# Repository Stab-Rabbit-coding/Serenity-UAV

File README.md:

<div align="center">

# Serenity UAV

### A flight-worthy, security-hardened EDF tilt-rotor replica of the Firefly-class ship *Serenity*

*"Can't stop the signal, and can't take the sky from me."*

*Isometric render of the Rev S assembly — port/bow/dorsal view. Predates the Rev S1g wing
spar and Rev S4c nacelle geometry; re-render pending (see `TODO.md` §0.10).*

</div>

## Overview

Serenity UAV is a fully functional electric ducted fan (EDF) tilt-rotor aircraft engineered as an
actual physical build of the Firefly-class transport *Serenity* (Joss Whedon, 2002) — every
component here is fabricated or procured, not conceptual. A two-part SLS-printed hull (one-piece forward head+cargo section and one-piece aft middle+rear section) carries two tilting EDF nacelles, a belly cargo bay with powered winch and clamshell doors,
and an 8-node cooperative avionics architecture with PACE (Primary/Alternate/Contingency/Emergency)
failover across every flight-critical function.

The design is held to the same rigor as a certifiable aircraft: real mass/CG/load budgets (no
"TBD" specs), FAA/FCC/NIST/IEC standards vetting on every design decision with any effect beyond
cosmetics, redundant power and control paths throughout, and a zero-trust security model — every
onboard message is signed, authenticated, and logged to hardware-enforced non-executable storage —
engineered to keep operating correctly inside a 500 W/m² RF field. Avionics, comms, and software
are built for reuse across other UAV/UGV/USV platforms, not just this airframe. See
[`AGENTS.md`](AGENTS.md) for the full authoritative project policy that governs every design
decision in this repository.

<table>
<tr>
<td width="50%" valign="top">

### Nominal Mission Profile

1. Take off VTOL.
2. Land vertically with cargo bay open and load and secure a 4″ × 3″ × 3″, 8 oz payload.
3. Take off VTOL with payload.
4. Fly into a 500 W/m² broadband RF environment.
5. Lower and release the payload from the cargo bay onto a platform.
6. Identify a 4″ × 3″ × 3″ payload on a moving platform.
7. Synchronize flight with the platform.
8. Attach the payload to the hoist and lift it from the platform.
9. Pull the payload into the cargo bay and close the clamshells.
10. Exit the hazardous environment and return to origin.

Throughout the mission, the aircraft shall also:

- Identify, categorize, log, and report rogue or unauthorized C2 commands or malicious logic from
  any transmitter, authorized or not.
- Identify unauthorized or unsafe behavior from any onboard compute node.
- Isolate the affected node(s), gracefully fail over its functions, and log/report to ground
  control — all while maintaining safety of flight.

</td>
<td width="50%" valign="top">

### Specifications

| Parameter | Value |
|-----------|-------|
| Length | 24.0 in (609 mm) |
| Wingspan | 19.1 in (486 mm) |
| Height | 7.93 in (201.5 mm) |
| AUW — two cells + 8 oz payload (Rev T-SB) | 13.93 lbm (6,318 g), provisional (`docs/flight_envelope.md`) |
| AUW — Phase 11 (full system) | not re-derived since the 64 mm / split-battery redesign |
| Payload capacity (minimum) | 8.0 oz (226 g) in a 4″ × 3″ × 3″ bay |
| Thrust — nacelles only | 20.90 lbf (9,480 g) = 4 × 83.60 ozf (2,370 gf), QF2822-2300KV at 24 V, 80 A ESCs |
| Thrust — Phase 11 rear EDF (cruise) | ~2.81 lbf (1,275 g) net after RCS bleed |
| T/W — nacelles only (hover) | ≈ 1.50 with payload (design floor 1.2; provisional pending mass truth) |
| T/W — Phase 11 (hover, nacelles only) | not re-derived |
| Compute | 8× PocketBeagle 2 Industrial (AM6254), PACE failover |
| Onboard buses | CAN FD, MIL-STD-1553C, RS-485, Ethernet RSTP ring |
| External comms | Five C2 links: Wi-Fi 5 GHz, Zigbee 2.4 GHz, mLRS, SiK/MAVLink 915 MHz, 49 MHz AX.25 |
| EMI design objective | 500 W/m² RF field, correct operation |

*Mass/thrust/T-W figures are the corrected 2026-08-22 baseline (the earlier 1.61 hover T/W used a
stale 2,768 g AUW) and remain provisional until the bottom-up AUW ledger recompute closes — see
`current-specification/README.md` and `docs/WBS.md` §0.10.1.*

</td>
</tr>
</table>

## Project Status (2026-11-03)

**Rev U, design and PCB layout. Nothing is fabricated or assembled; the physical build has not
started.** The path to first flight is in `docs/FIRST_FLIGHT_READINESS.md`; open work is in
[`TODO.md`](TODO.md), generated from the full record in [`WBS.md`](WBS.md).

| Area | State |
|------|-------|
| Airframe | SCAD shells at Rev S baseline, carried into Rev U; STL re-exports pending after the TACCO 60 × 35 mm change; cargo-shell mesh defect open |
| Nacelles | The 64 mm tandem-EDF nacelle (NAC-64-SERVO-01) with a servo-driven nozzle is the Rev U nacelle; the 50 mm nacelle is archived. Pivot (residual +9.6 mm), CFD, mass, and bench gates are open; the published pod STLs need a re-bake, and the 64 mm ESC bay covers are not yet generated (`tools/check_nacelle_deps.py`) |
| Avionics PCBs | Pilot and TACCO placed with ERC 0 / DRC 0 before routing, on corrected 4.80 mm PB2 rails; routing and Gerbers open. Flight Engineer, Observer, and Commo Rev T need further PCB work |
| Buses | Fleet MIL-STD-1553C via the Holt HI-6138 on every Pilot and TACCO (2026-09-28) |
| Comms | mLRS on a bare STM32WLE5JC; Wi-Fi USB module selection is a fab blocker; Commo becomes one standalone node (Rev T, 2026-09-29) |
| Firmware | `serenity-cn` Phase 6 done; `serenity-fc` Phase 6 stub; Phase 7 open |
| Ground station | Skipper in design; ground-side radio loadout decision open |
| BOM | `bom_revU` published 2026-11-03 (carry-forward of `bom_revT`, 2026-09-28); avionics rows lag the 2026-10 PCB changes |
| Build guide | Hand-drawn pre-Rev-T art; rebuild open (task 1.5.6) |

## Subsystems

<table>
<tr>
<td width="50%" valign="top">
<br><br>

**Airframe**

SLS-printed (DuraForm PA CF) hull with high-lift wings: in two sections (forward head+cargo and aft middle+rear), hollow-walled
and foam-filled to the canonical Firefly outer mold line. Rev S1g gave the wing a fixed,
bonded 20×16.3 mm carbon-fiber spar as its primary bending member, replacing the earlier
rotating-shaft design.

[Airframe README →](airframe/README.md)

</td>
<td width="50%" valign="top">
<br><br>

**Landing Gear**

Four corner legs pair a rigid CF-PETG post with spring and ductile wire braces, giving a
deliberately progressive, field-replaceable failure mode rated for a 6 ft full-AUW drop.

[Landing Gear Analysis →](docs/LANDING_GEAR_ANALYSIS.md)

</td>
</tr>
<tr>
<td width="50%" valign="top">
<br><br>

**Nacelles**

Two tilting pods each carry a tandem 64 mm EDF pair (QX-Motor QF2822-2300KV, 2,370 gf each), with a
variable-area nozzle scheduled on measured tilt (−5° to +135° pivot; 0° = horizontal) and driven by one KST X06
sub-micro servo per pod. The 64 mm pod is a uniform ×1.06 enlargement of the canonical shell with an integral
stage-1 motor plate and a removable stage-2 cartridge. The earlier 50 mm pods (Rev S4c) are archived.

[Nozzle-Drive Trade Study →](docs/NOZZLE_DRIVE_TRADE.md)

</td>
<td width="50%" valign="top">
<br><br>

**Powerplant**

Four nacelle EDFs give 9.84 lbf combined hover thrust at a T/W of ≈1.14, fed by a 6S LiPo through
the EMI-hardened Flight Engineer power distribution board.

[Power Distribution →](docs/POWER_DISTRIBUTION.md)

</td>
</tr>
<tr>
<td width="50%" valign="top">
<br><br>

**Avionics**

Eight PocketBeagle 2 Industrial nodes in four PACE-redundant stacks handle flight control, comms,
and payload functions, all with 5 kV galvanic isolation, TPM-backed signed logging, MIL-STD-1553C,
and a standalone **Commo** radio node (Rev T), plus the **Skipper** ground control station.

[Avionics README →](avionics/README.md)

</td>
<td width="50%" valign="top">
<br><br>

**Bow Sensor Suite**

The forward **Observer** node — camera, Time-of-Flight array, and an eye-safe laser indicator — in
the nose pod handles obstacle avoidance and rough size/orientation sizing of the mission payload.

[Observer Board →](avionics/kicad/Observer/Observer.md)

</td>
</tr>
<tr>
<td colspan="2" valign="top">
<br><br>

**Cargo Handling — Observer**

A belly clamshell cargo bay with a powered winch and hoist loads/releases an 8 oz payload in
flight, guided by the downward-facing **Observer** node for close-in 3D imaging of the payload.

[Cargo Winch Specification →](docs/CARGO_WINCH_SPECIFICATION.md)

</td>
</tr>
</table>

---

## Table of Contents

- [Project Status](#project-status-2026-10-07)
- [Authoritative Project Instructions](#authoritative-project-instructions)
- [References](#references)
- [License](#license)
- [Attribution](#attribution)
    - [Component License Map](#component-license-map)
    - [What This License Covers](#what-this-license-covers)
    - [Patent Notice](#patent-notice)
    - [Forensic Evidence Integrity Note](#forensic-evidence-integrity-note)

---

## Authoritative Project Instructions

The canonical workspace instructions and design policy are maintained in `AGENTS.md`. All
contributors and automated tools (including AI assistants) shall follow the requirements and
standards documented there (coding style, fabrication specs, licensing, and attribution).
`CLAUDE.md` is a one-line pointer to the same file, kept for tooling that looks for that name.

The [Nominal Mission Profile](#nominal-mission-profile) and [Specifications](#specifications)
above are the current design baseline. Full engineering detail for each subsystem lives in that
subsystem's own README/doc — see the link on each card in [Subsystems](#subsystems) above. The
narrative that used to live directly in this file (full Airframe/Powerplant/Avionics/Cargo
Handling write-ups) is preserved verbatim, for historical reference, in
[`archives/root-readme-deep-dive-2026-08-03.tar.gz`](archives/MANIFEST.md) (unpack per [`archives/README.md`](archives/README.md)).

---

## References

- Design conversation: [claude.ai/share/a1e3900e-d2bf-4690-ba63-25178e7de666](https://claude.ai/share/a1e3900e-d2bf-4690-ba63-25178e7de666)
- Latest design revision BOM: `current-specification/bom_revU.json` (Rev U, 2026-11-03)

---

## License

Licensed by Steve Griffing, PE(CSE), CISSP-ISSEP, CPP, according to what each file produces:

- **Hardware — and any code that defines, creates or renders hardware** (OpenSCAD,
  KiCad files and scripts, FreeCAD, Blender, G-code/slicer profiles, and tools that
  write or render meshes/CAD/PCB) — **CERN-OHL-W 2.0** (SPDX `CERN-OHL-W-2.0`).
  Full text: `LICENSE` (root) / `LICENSES/CERN-OHL-W 2.0`.
- **Code whose end result is software or firmware** (firmware, device trees, ground
  software, analysis/verification/CI tools) — **MIT** (SPDX `MIT`). Full text:
  `LICENSES/MIT`.
- **Documents** (Markdown, text, specifications, build guides, and all images — SVG,
  PNG, JPG, WebP, including renders produced by hardware tools) — **CC BY-SA 4.0**
  (SPDX `CC-BY-SA-4.0`). Full text: `LICENSES/CC-BY-SA 4.0`.

See `docs/attribution_and_licensing.md` for the full policy, the per-subsystem `LICENSE`
federation map, and the CERN-OHL-W "Available Component" treatment of upstream
canonical-reference geometry. Revision U, November 2026.

## Attribution

> "Serenity Tiltrotor Drone Project — hardware CERN-OHL-W 2.0, software MIT, docs CC BY-SA 4.0, based on:
> · Serenity Firefly-class hull by misubisu (thingiverse.com/thing:7330462, CC BY-SA 4.0)
> · Variable-area EDF nozzle by BamJr (thingiverse.com/thing:2991269, CC BY 4.0)
> Include a link to the applicable license and indicate if changes were made."

### Component License Map

| Component | Original Author | Source | License | Derivative Notes |
|-----------|----------------|--------|---------|-----------------|
| Hull | misubisu | [thingiverse.com/thing:7330462](https://www.thingiverse.com/thing:7330462) | CC BY-SA 4.0 (Available Component under CERN-OHL-W 2.0) | Scaled to 24 in, hollowed to 0.079 in (2.0 mm) CF-PETG shell, foam-filled |
| Nozzle mechanism concept | BamJr | [thingiverse.com/thing:2991269](https://www.thingiverse.com/thing:2991269) | CC BY 4.0 | Iris petal concept reference; all Rev O/P/Q nozzle geometry original |
| Design (hardware/CAD/PCB) | This project | — | CERN-OHL-W 2.0 | All original work: PCBs, mechanical/CAD, wiring |
| Design (docs/code/scripts) | This project | — | CC BY-SA 4.0 | Firmware spec, tooling, build guides, this document |

### What This License Covers

Covered under **CERN-OHL-W 2.0** (hardware):

- 3D-printable hull, nacelle, and nozzle design files (STL/SCAD/FCStd)
- PCB schematics and Gerber files for Pilot, TACCO, Flight Engineer, Commo, and Observer
- Circuit diagrams, pinout tables, and wiring specifications
- Mechanical drawings and assembly specifications
- Any derived hardware shall carry CERN-OHL-W 2.0 (or a compatible license) and attribute
  all upstream authors

Covered under **CC BY-SA 4.0** (documentation, code, scripts, non-hardware drawings):

- Firmware architecture specifications and algorithm descriptions
- This design document in all its revisions (A–R and beyond)
- Build automation/tooling scripts and non-hardware SVG diagrams
- Any derived works shall carry CC BY-SA 4.0 and attribute all upstream authors

Not covered / separate terms:

- Third-party commercial components (EDFs, ESCs, PocketBeagle 2, etc.) — their own terms
- SiK radio firmware — GPL-3.0
- ArduPilot / QGroundControl — GPL-3.0
- tpm2-tools / tpm2-tss — BSD-2
- CPLD Verilog write-blocker firmware — separately MIT licensed
- Proprietary flight controller firmware (your compiled code) — your terms
- FAA/ICAO regulatory compliance is YOUR responsibility as operator

### Patent Notice

This license does NOT grant rights to any patents held by component manufacturers or the
design authors. The design uses standard open hardware interfaces (CAN FD, Ethernet, SDIO,
SPI, I²C, MAVLink). If you commercialise products based on this design, conduct your own
freedom-to-operate analysis. The write-blocker CPLD design implements append-only log
enforcement consistent with log data protection principles in NIST SP 800-92 §4.4.2
[REF-NIST-004]; no patent claims are made on the implementation.

### Forensic Evidence Integrity Note

The write-blocker and NX enforcement hardware described in this design are intended to
support operational log integrity, not forensic evidence collection.  They implement
log data protection principles consistent with NIST SP 800-92 §4.4.2 [REF-NIST-004].
They are NOT certified forensic tools under NIST CFTT (Computer Forensics Tool Testing)
Program specifications or SWGDE (Scientific Working Group on Digital Evidence) standards.
Do not use this design as the sole mechanism for evidence preservation in legal proceedings
without independent verification of the implementation against your jurisdiction's
evidence handling requirements.

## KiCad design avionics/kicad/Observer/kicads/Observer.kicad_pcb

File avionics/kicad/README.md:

# Serenity Avionics — KiCad Board Index and Status

**Last updated:** 2026-10-07
**License:** CC BY-SA 4.0 — creativecommons.org/licenses/by-sa/4.0 (SPDX-License-Identifier: CC-BY-SA-4.0)

This directory holds the KiCad projects, generator scripts, and status files for every Serenity
avionics board. **Each board's own `.md` file is the authoritative as-built status**
(`avionics/AGENTS.md`, "Cape Naming and Revision History"); the table below is a dated
snapshot, so confirm against the board file before relying on it for fabrication or integration.
KiCad files keep KiCad board coordinates (a documented exception to the hull-frame standard,
see root `AGENTS.md`).

## Boards

| Folder | Board | Role | Status file |
| --- | --- | --- | --- |
| `Pilot/` | **Pilot** | PB2-I cape: flight control and sensors | `Pilot/Pilot.md` |
| `TACCO/` | **TACCO** | PB2-I cape: comms, logging, payload | `TACCO/TACCO.md` |
| `FlightEngineer/` | **Flight Engineer** | Power Distribution Board (PDB) | `FlightEngineer/FlightEngineer.md` |
| `Commo/` | **Commo** | 49 MHz + SiK transceiver; Rev S was a PB2-I cape, Rev T is a standalone bus node | `Commo/Commo.md` |
| `Observer/` | **Observer** | Standalone nose/cargo-bay vision, ToF, and laser board | `Observer/Observer.md` |
| `Bus-Gateway/` | **CAN-PERIPH-GW-1** | Secure CAN-FD / RS-485 edge node | `Bus-Gateway/CAN-PERIPH-GW-1.md` |
| `Encoder/` | **ENC-NACELLE-1** | Nacelle tilt-angle encoder (AK7455) | `Encoder/ENC-NACELLE-1.md` |

The legacy working name "XO" for TACCO survives only in some script and file names.

## Status snapshot (2026-10-07)

| Board | ERC | DRC | Placement | Routing | Gerbers |
| --- | --- | --- | --- | --- | --- |
| Pilot | 0 errors | 0 errors, parity 0 | 120 of 120 placed | Not started (0% routed) | Open |
| TACCO | 0 errors | 0 errors, parity 0 (before routing) | 163 parts placed on a 60 × 35 mm outline | Not started (0 segments) | Open; the checked-in set predates the rebuild |
| Flight Engineer | 0 errors | 29–31 hard violations | 151 of 151 placed | Not started | Open |
| Commo | Rev S: 0 errors | Rev S closed, not worked further | Rev T in design | Rev T outline and placement open | Rev S Gerbers will not be built |
| Observer | 0 errors | 124 hard violations | Initial shelf-pack; PCB predates the schematic | Not started; PCB resync not started | Open |
| Bus-Gateway | 0 errors | 1 hard violation | Placed (`N_STACKS=4`) | About 84% routed | Generated at that state |
| Encoder | 0 errors | 0 hard violations | Complete | Complete | Open item: firmware and bench calibration |

Pilot and TACCO both use Samtec TSM-118-04-L-DV-LC male SMT rails at 4.80 mm from each long
board edge (PB2 System Reference Manual Fig. 3.45, REF-SENSOR-041). A fab blocker is open on
TACCO: the owner has yet to select the USB Wi-Fi module (`avionics/WBS.md` §1.2a). The open-item
list for every board is in `avionics/TODO.md`; the full record is `avionics/WBS.md`.

## Supporting files

| Path | Purpose |
| --- | --- |
| `PB2_HEADER_PINMAP.md` | Verified PocketBeagle 2 P1/P2 ball-by-ball map and the TACCO allocation |
| `HI6138_FOOTPRINT_VERIFICATION.md` | Holt HI-6138 (MIL-STD-1553C) pin table and area budget |
| `Serenity-Custom.pretty/`, `symbols/` | Project footprint and symbol libraries |
| `tools/swap_1553_hi6138.py` | The fleet 1553C swap script (this folder's `tools/`) |
| `gerbers/` | Legacy Rev S1 Gerber sets; per-board sets are under each board folder (check its status file for currency) |
| `TODO-1.2b-*.md` | Archived (moved to `archives/rev-T-and-earlier/avionics/kicad/`): superseded 2026-07-18 task snapshots; the live record is `avionics/WBS.md` §1.2a |

## Design method

Pilot, TACCO, Flight Engineer, and the Bus-Gateway use a **schematic-first generator** workflow:
a Python generator under `<board>/scripts/` writes both the schematic and the PCB, so the two
stay in parity. Edit the generator, not the generated files, except where a board file says the
owner has taken manual control of placement. Final component placement is the owner's
(root `AGENTS.md` §5); refer any DRC violation that needs a footprint moved to the owner.
Every schematic or PCB edit needs a KiCad ERC and DRC pass (root `AGENTS.md` §7).

## Toolchain findings (headless KiCad 9 and freerouting)

Recorded so the next contributor does not re-derive them:

- **`pcbnew.ExportSpecctraDSN()` does not work in standalone Python** under KiCad 9.0.2: it
  returns `False` because there is no GUI context. The project uses a custom headless Specctra
  DSN exporter and SES importer (repo-root `tools/export-specctra-dsn.py`, `tools/import-specctra-ses.py`)
  that round-trip correctly.
- **freerouting 2.2.4** exits by itself after its passes and gave the Bus-Gateway its ~84%
  route. Run it without a display, with `-mt 1`. It writes the `.ses` only at the end of a run,
  and its passes take minutes each, so budget the full run. The earlier 2.1.0 build never
  self-exited and captured only a handful of nets; do not use it.
- **Pilot's two runs were rejected** (see "Routing status" in `Pilot/Pilot.md`): automated
  results that introduced shorts are reported, not accepted.
- Route the impedance-controlled Ethernet pairs interactively, length-matched, regardless of
  autorouter results.
- The tamper-mesh rework (per-domain meshes, tamper signals for TPM-less boards) is open
  work in `avionics/WBS.md` §1.2a.1.

---

*Author: Steve Griffing, PE(CSE), CISSP-ISSEP, CPP · License: CC BY-SA 4.0*

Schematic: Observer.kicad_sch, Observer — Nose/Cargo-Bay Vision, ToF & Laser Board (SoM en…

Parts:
CMC5: SRF2012-100Y (CAN); L_CommonModeChoke_Coilcraft_0805USB
C_2V5I, C_2V5O: 1uF; C_0402_1005Metric
C_ADM1, C_ADM2: 100nF; C_0402_1005Metric
C_ISO: 100nF/500V; C_0402_1005Metric
C_VCORE: 1uF; C_0402_1005Metric
C_VISO: 1uF; C_0402_1005Metric
D5: PRTR5V0U2X; SOT-143
J_CAM1: CSI CLK/D0; JST_GH_BM04B-GHS-TBT_1x04-1MP_P1.25mm_Vertical
J_CAM2: CAM SDA/SCL/RST/3V3; JST_GH_BM04B-GHS-TBT_1x04-1MP_P1.25mm_Vertical
J_CAM_DS: Direct-solder camera land (nose; DNP if J_CAM* us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; DS_Camera_9P
J_CANFD: 5V/CANH/CANL/GND; JST_GH_BM04B-GHS-TBT_1x04-1MP_P1.25mm_Vertical
J_CHASSIS_R: 0R; R_0402_1005Metric
J_ETH_IN: JST-GH 5P shielded Eth ring; JST_GH_SM05B-GHS-TB_1x05-1MP_P1.25mm_Horizontal
J_ETH_OUT: JST-GH 5P shielded Eth ring; JST_GH_SM05B-GHS-TB_1x05-1MP_P1.25mm_Horizontal
J_LASER: laser +5V/cathode; JST_SH_BM02B-SRSS-TB_1x02-1MP_P1.00mm_Vertical
J_LASER_DS: Direct-solder laser land (nose; DNP if J_LASER us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; DS_Laser_2P
J_PWR: JST-GH 2P +5V/GND; JST_GH_BM02B-GHS-TBT_1x02-1MP_P1.25mm_Vertical
J_RS485_IN: RS-485 trunk IN (A/B/GND)
J_RS485_OUT: RS-485 trunk OUT (A/B/GND)
J_SWD: SWD: DIO/CLK/NRST/GND; JST_GH_BM04B-GHS-TBT_1x04-1MP_P1.25mm_Vertical
J_TOF: TFmini-S 5V/GND/TX/RX; JST_GH_BM04B-GHS-TBT_1x04-1MP_P1.25mm_Vertical
J_TOF_DS: Direct-solder ToF land (nose; DNP if J_TOF used); DS_ToF_4P
Q1: AO3400 logic-level N-MOSFET; SOT-23
R1: 100R gate; R_0402_1005Metric
R2: 10k pulldown; R_0402_1005Metric
R_485TERM: 120R; R_0402_1005Metric
R_FB1B, R_FB1T, R_FB3B: 100k 1%; R_0402_1005Metric
R_FB3T: 453k 1%; R_0402_1005Metric
R_ISET: 6.04k; R_0402_1005Metric
R_NRST: 10k; R_0402_1005Metric
R_PG1, R_PG3: 100k; R_0402_1005Metric
R_PORZ: 10k; R_0402_1005Metric
R_REXT: 191R; R_0402_1005Metric
R_SHIELD: 0R; R_0402_1005Metric
SJ_485: open by default; SolderJumper-2_P1.3mm_Open_Pad1.0x1.5mm
T1, T2: Wurth 749010012A; Wurth_749010012A_10-100BASE-TX
T1_CMC1, T1_CMC2, T2_CMC1, T2_CMC2: SRF2012-100Y; L_CommonModeChoke_Coilcraft_0805USB
T1_D1, T1_D2, T2_D1, T2_D2: PRTR5V0U2X; SOT-143
U2: Microchip KSZ9477; TQFP-128-1EP_KSZ9477_14x14mm_P0.4mm_EP10x10
U3: TI MSPM0G3519-Q1; VQFN-48-1EP_7x7mm_P0.5mm_EP4.1x4.1mm
U4: TI ISOW1044BDFMR; SOIC-20W_7.5x12.8mm_P1.27mm
U5: Infineon SLB 9672AU2.0; QFN-32-1EP_5x5mm_P0.5mm_EP3.6x3.6mm
U6: TI ISOW1412; SOIC-20W_7.5x12.8mm_P1.27mm
U_REG_1V2, U_REG_3V3: TLV62569PDRLR; SOT-563
U_REG_1V2_CI, U_REG_3V3_CI: 10uF; C_0402_1005Metric
U_REG_1V2_CO, U_REG_3V3_CO: 22uF; C_0402_1005Metric
U_REG_1V2_L, U_REG_3V3_L: 2.2uH; L_Taiyo-Yuden_NR-20xx
U_REG_2V5: TLV75725PDRVR; WSON-6-1EP_2x2mm_P0.65mm_EP1x1.6mm
U_SOM: phyCORE-AM62x PCM-071; phyCORE-AM62x_PCM071_2xBTH-060
Y1: 25MHz; Crystal_SMD_2012-2Pin_2.0x1.2mm

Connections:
+1V2: R_FB1T.1, R_PG1.1, U2.3 (AVDDL), U2.11 (DVDDL), U2.14 (AVDDL), U2.19 (AVDDL), U2.23 (DVDDL), U2.30 (AVDDL), U2.36 (AVDDL), U2.41 (AVDDL), U2.45 (DVDDL), U2.56 (DVDDL), U2.66 (DVDDL), U2.70 (DVDDL), U2.71 (VDDLS), U2.84 (VDDLS), U2.87 (DVDDL), U2.104 (DVDDL), U2.110 (DVDDL), U2.114 (AVDDL), U2.119 (AVDDL), U2.124 (AVDDL), U_REG_1V2_CO.1, U_REG_1V2_L.2
+1V2_PG: R_PG1.2, U_REG_1V2.6 (PG)
+2V5: C_2V5O.1, U2.10 (AVDDH), U2.22 (AVDDH), U2.33 (AVDDH), U2.44 (AVDDH), U2.72 (VDDHS), U2.83 (VDDHS), U2.111 (AVDDH), U2.122 (AVDDH), U2.128 (AVDDH), U_REG_2V5.1 (OUT)
+3V3: C_2V5I.1, C_ADM1.1, J_CAM2.4, J_CAM_DS.8, R_FB3T.1, R_NRST.1, R_PG3.1, R_PORZ.1, U2.61 (VDDIO), U2.68 (VDDIO), U2.99 (VDDIO), U3.6 (VDD), U4.1 (VIO), U5.7 (GPIO_02), U5.8 (NCI/VDD), U5.22 (VDD), U6.1 (VIO), U6.9 (VDD), U_REG_2V5.4 (EN), U_REG_2V5.6 (IN), U_REG_3V3_CO.1, U_REG_3V3_L.2, U_SOM.B1 (SoC_VDDSHV5_SDIO), U_SOM.B2 (VBAT)
+3V3_PG: R_PG3.2, U_REG_3V3.6 (PG)
+5V: J_CANFD.1, J_LASER.1, J_LASER_DS.1, J_PWR.2, J_TOF.1, J_TOF_DS.1, U4.9 (VDD), U_REG_1V2.3 (VIN), U_REG_1V2.5 (EN), U_REG_1V2_CI.1, U_REG_3V3.3 (VIN), U_REG_3V3.5 (EN), U_REG_3V3_CI.1, U_SOM.A1 (VIN), U_SOM.A2 (VIN), U_SOM.A3 (VIN)
CAM_RESET_N: J_CAM2.3, J_CAM_DS.7, U_SOM.A56 (X_WKUP_UART0_CTSN)
CAM_SCL: J_CAM2.2, J_CAM_DS.6, U_SOM.C32 (X_I2C1_SCL)
CAM_SDA: J_CAM2.1, J_CAM_DS.5, U_SOM.C33 (X_I2C1_SDA)
CANFD_H: CMC5.2 (L1B), D5.2 (IO1), J_CANFD.2
CANFD_ISOGND: C_VISO.2, U4.11 (GND2), U4.15 (GISOIN), U4.16 (GISOIN), U4.17 (GISOIN)
CANFD_ISO_H: CMC5.1 (L1A), U4.19 (CANH)
CANFD_ISO_L: CMC5.3 (L2A), U4.18 (CANL)
CANFD_L: CMC5.4 (L2B), D5.3 (IO2), J_CANFD.3
CANFD_RX: U3.28 (PA13), U4.5 (RXD)
CANFD_TX: U3.27 (PA12), U4.3 (TXD)
CANFD_VISO: C_VISO.1, U4.12 (VISOOUT), U4.13 (VSIN), U4.20 (VISOIN)
CSI_CLK_N: J_CAM1.2, J_CAM_DS.2, U_SOM.B32 (X_CSI0_RXCLKN)
CSI_CLK_P: J_CAM1.1, J_CAM_DS.1, U_SOM.B31 (X_CSI0_RXCLKP)
CSI_D0_N: J_CAM1.4, J_CAM_DS.4, U_SOM.A36 (X_CSI0_RXN0)
CSI_D0_P: J_CAM1.3, J_CAM_DS.3, U_SOM.A35 (X_CSI0_RXP0)
ETH_IN_KSZ_RXN: T1.4 (PHY_RXN), U2.5 (TXRX1M_B)
ETH_IN_KSZ_RXP: T1.3 (PHY_RXP), U2.4 (TXRX1P_B)
ETH_IN_KSZ_TXN: T1.2 (PHY_TXN), U2.2 (TXRX1M_A)
ETH_IN_KSZ_TXP: T1.1 (PHY_TXP), U2.1 (TXRX1P_A)
ETH_IN_LRXN: T1.8 (LINE_RXN), T1_CMC2.3 (L2A)
ETH_IN_LRXP: T1.7 (LINE_RXP), T1_CMC2.1 (L1A)
ETH_IN_LTXN: T1.6 (LINE_TXN), T1_CMC1.3 (L2A)
ETH_IN_LTXP: T1.5 (LINE_TXP), T1_CMC1.1 (L1A)
ETH_IN_RXN: J_ETH_IN.5, T1_CMC2.4 (L2B), T1_D2.3 (IO2)
ETH_IN_RXP: J_ETH_IN.4, T1_CMC2.2 (L1B), T1_D2.2 (IO1)
ETH_IN_TXN: J_ETH_IN.3, T1_CMC1.4 (L2B), T1_D1.3 (IO2)
ETH_IN_TXP: J_ETH_IN.2, T1_CMC1.2 (L1B), T1_D1.2 (IO1)
ETH_OUT_KSZ_RXN: T2.4 (PHY_RXN), U2.16 (TXRX2M_B)
ETH_OUT_KSZ_RXP: T2.3 (PHY_RXP), U2.15 (TXRX2P_B)
ETH_OUT_KSZ_TXN: T2.2 (PHY_TXN), U2.13 (TXRX2M_A)
ETH_OUT_KSZ_TXP: T2.1 (PHY_TXP), U2.12 (TXRX2P_A)
ETH_OUT_LRXN: T2.8 (LINE_RXN), T2_CMC2.3 (L2A)
ETH_OUT_LRXP: T2.7 (LINE_RXP), T2_CMC2.1 (L1A)
ETH_OUT_LTXN: T2.6 (LINE_TXN), T2_CMC1.3 (L2A)
ETH_OUT_LTXP: T2.5 (LINE_TXP), T2_CMC1.1 (L1A)
ETH_OUT_RXN: J_ETH_OUT.5, T2_CMC2.4 (L2B), T2_D2.3 (IO2)
ETH_OUT_RXP: J_ETH_OUT.4, T2_CMC2.2 (L1B), T2_D2.2 (IO1)
ETH_OUT_TXN: J_ETH_OUT.3, T2_CMC1.4 (L2B), T2_D1.3 (IO2)
ETH_OUT_TXP: J_ETH_OUT.2, T2_CMC1.2 (L1B), T2_D1.2 (IO1)
GND: C_2V5I.2, C_2V5O.2, C_ADM1.2, C_ISO.1, C_VCORE.2, J_CAM_DS.9, J_CANFD.4, J_CHASSIS_R.1, J_PWR.1, J_SWD.4, J_TOF.2, J_TOF_DS.2, Q1.2 (S), R2.2, R_FB1B.2, R_FB3B.2, R_ISET.2, R_REXT.2, T1_D1.1 (GND), T1_D1.4 (VCC), T1_D2.1 (GND), T1_D2.4 (VCC), T2_D1.1 (GND), T2_D1.4 (VCC), T2_D2.1 (GND), T2_D2.4 (VCC), U2.46 (GND), U2.47 (GND), U2.69 (GND), U2.75 (GND), U2.77 (GND), U2.80 (GND), U2.107 (GND), U2.109 (GND), U2.123 (GND), U2.129 (GND), U3.7 (VSS), U3.49 (VSS), U4.4 (STB), U4.6 (GNDIO), U4.10 (GND1), U5.2 (GND), U5.9 (GND), U5.23 (GND), U5.32 (GND), U5.33 (GND), U6.6 (GNDIO), U6.10 (GND1), U_REG_1V2.2 (GND), U_REG_1V2_CI.2, U_REG_1V2_CO.2, U_REG_2V5.3 (GND), U_REG_2V5.7 (EP), U_REG_3V3.2 (GND), U_REG_3V3_CI.2, U_REG_3V3_CO.2, U_SOM.A4 (GND), U_SOM.A9 (GND), U_SOM.A14 (GND), U_SOM.A19 (GND), U_SOM.A24 (GND), U_SOM.A29 (GND), U_SOM.A32 (GND), U_SOM.A37 (GND), U_SOM.A42 (GND), U_SOM.A45 (GND), U_SOM.A50 (GND), U_SOM.A55 (GND), U_SOM.B3 (GND), U_SOM.B8 (GND), U_SOM.B13 (GND), U_SOM.B18 (GND), U_SOM.B23 (GND), U_SOM.B28 (GND), U_SOM.B33 (GND), U_SOM.B38 (GND), U_SOM.B43 (GND), U_SOM.B48 (GND), U_SOM.B53 (GND), U_SOM.B56 (GND), U_SOM.B60 (GND), U_SOM.C6 (GND), U_SOM.C12 (GND), U_SOM.C19 (GND), U_SOM.C24 (GND), U_SOM.C31 (GND), U_SOM.C38 (GND), U_SOM.C43 (GND), U_SOM.C48 (GND), U_SOM.C53 (GND), U_SOM.C59 (GND), U_SOM.D3 (GND), U_SOM.D9 (GND), U_SOM.D17 (GND), U_SOM.D22 (GND), U_SOM.D27 (GND), U_SOM.D34 (GND), U_SOM.D39 (GND), U_SOM.D45 (GND), U_SOM.D52 (GND), U_SOM.D57 (GND)
ISO_3V3_485: C_ADM2.1, U6.12 (VISOOUT), U6.16 (VISOIN)
ISO_GND_485: C_ADM2.2, J_RS485_IN.3, J_RS485_OUT.3, U6.11 (GND2), U6.13 (MODE), U6.15 (GISOIN)
KSZ_ISET: R_ISET.1, U2.127 (ISET)
KSZ_SREXT: R_REXT.1, U2.76 (S_REXT)
KSZ_XI: U2.126 (XI), Y1.1
KSZ_XO: U2.125 (XO), Y1.2
LASER_CATHODE: J_LASER.2, J_LASER_DS.2, Q1.3 (D)
LASER_EN: R1.1, U3.40 (PA22)
LASER_GATE: Q1.1 (G), R1.2, R2.1
MCU_NRST: J_SWD.3, R_NRST.2, U3.4 (NRST)
MCU_SWCLK: J_SWD.2, U3.35 (PA20/SWCLK)
MCU_SWDIO: J_SWD.1, U3.34 (PA19/SWDIO)
MCU_VCORE: C_VCORE.1, U3.48 (VCORE)
PGND: C_ISO.2, D5.1 (GND), D5.4 (VCC), J_CHASSIS_R.2, R_SHIELD.1
PGND_SHIELD: J_ETH_IN.1, J_ETH_OUT.1, R_SHIELD.2
RGMII_K2S_C: U2.48 (TX_CLK6/REFCLKI6), U_SOM.A18 (X_CPSW_RGMII2_RXC)
RGMII_K2S_CTL: U2.49 (TX_EN6/TX_CTL6), U_SOM.A17 (X_CPSW_RGMII2_RX_CTL)
RGMII_K2S_D0: U2.55 (TXD6_0), U_SOM.A23 (X_CPSW_RGMII2_RD0)
RGMII_K2S_D1: U2.54 (TXD6_1), U_SOM.A22 (X_CPSW_RGMII2_RD1)
RGMII_K2S_D2: U2.53 (TXD6_2), U_SOM.A21 (X_CPSW_RGMII2_RD2)
RGMII_K2S_D3: U2.52 (TXD6_3), U_SOM.A20 (X_CPSW_RGMII2_RD3)
RGMII_S2K_C: U2.57 (RX_CLK6/REFCLKO6), U_SOM.A25 (X_CPSW_RGMII2_TXC)
RGMII_S2K_CTL: U2.58 (RX_DV6/CRS_DV6/RX_CTL6), U_SOM.A26 (X_CPSW_RGMII2_TX_CTL)
RGMII_S2K_D0: U2.65 (RXD6_0), U_SOM.A27 (X_CPSW_RGMII2_TD0)
RGMII_S2K_D1: U2.64 (RXD6_1), U_SOM.A28 (X_CPSW_RGMII2_TD1)
RGMII_S2K_D2: U2.63 (RXD6_2), U_SOM.A30 (X_CPSW_RGMII2_TD2)
RGMII_S2K_D3: U2.62 (RXD6_3), U_SOM.A31 (X_CPSW_RGMII2_TD3)
RS485_A: J_RS485_IN.1, J_RS485_OUT.1, R_485TERM.1, U6.17 (Y), U6.20 (A)
RS485_B: J_RS485_IN.2, J_RS485_OUT.2, SJ_485.2, U6.18 (Z), U6.19 (B)
RS485_DE: U3.14 (PB2), U6.3 (DE), U6.5 (RE_N)
RS485_FLT_N: U6.8 (EN_FLT)
RS485_RX: U3.26 (PB16), U6.4 (R)
RS485_TX: U3.25 (PB15), U6.2 (D)
SOC_PORZ: R_PORZ.2, U_SOM.C52 (X_nRESET_IN)
SW_INT_N: U2.94 (INTRP_N), U3.45 (PA25)
SW_RESET_N: U2.96 (RESET_N), U3.39 (PA21)
SW_SPI_CS: U2.100 (SCS_N), U3.30 (PA15)
SW_SPI_MISO: U2.97 (SDO), U3.31 (PA16)
SW_SPI_MOSI: U2.98 (SDI/SDA/MDIO), U3.33 (PA18)
SW_SPI_SCK: U2.101 (SCL/MDC), U3.32 (PA17)
TERM485_MID: R_485TERM.2, SJ_485.1
TPM_PIRQ: U3.46 (PA26), U5.18 (PIRQ#)
TPM_RESET_N: U3.47 (PA27), U5.17 (RST#)
TPM_SPI_CS: U3.8 (PA2), U5.20 (CS#)
TPM_SPI_MISO: U3.10 (PA4), U5.24 (MISO)
TPM_SPI_MOSI: U3.11 (PA5), U5.21 (MOSI)
TPM_SPI_SCK: U3.12 (PA6), U5.19 (SCLK)
UART_A2M: U3.19 (PA11), U_SOM.D38 (X_UART0_TXD)
UART_M2A: U3.18 (PA10), U_SOM.D37 (X_UART0_RXD)
UART_TOF_RX: J_TOF.4, J_TOF_DS.4, U3.17 (PA9)
UART_TOF_TX: J_TOF.3, J_TOF_DS.3, U3.16 (PA8)
U_REG_1V2_FB: R_FB1B.1, R_FB1T.2, U_REG_1V2.1 (FB)
U_REG_1V2_SW: U_REG_1V2.4 (SW), U_REG_1V2_L.1
U_REG_3V3_FB: R_FB3B.1, R_FB3T.2, U_REG_3V3.1 (FB)
U_REG_3V3_SW: U_REG_3V3.4 (SW), U_REG_3V3_L.1

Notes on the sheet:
OBSERVER — Nose/Cargo Vision/ToF/Laser | STANDALONE board (NOT a PB2-I cape) | SoM end-state: PHYTEC PCM-071 + carrier (KSZ9477 / MSPM0G3519-Q1 / SLB9672 / ISOW1044)
=== Section A: Power Input + Carrier Rails ===
Carrier rails (design decision 2026-07-13): PCM-071 provides NO rail to the carrier; all generated here from +5V. Feedback dividers / inductor / LDO margin are first-pass — verify per TI datasheet design procedures.
=== Section B: PHYTEC phyCORE PCM-071 SoM (U_SOM) ===
=== Section C: Microchip KSZ9477 (U2) ===
=== Section D: MSPM0G3519-Q1 (U3) + SLB 9672 TPM (U5) ===
=== Section E: ISOW1044 Isolated CAN-FD (U4) ===
=== Section F: Ethernet Ring EMI Chain (in / out) ===
=== Section G: PGND/GND single-point bond ===
=== Section H: Camera / ToF / Laser ===
=== Section H: ISOW1412 Isolated RS-485 (U6) ===
WÜRTH ELEKTRONIK USAGE NOTICE (verbatim, 749010012A data sheet rev 004.000 p.1; applies to Würth parts on this board: 749010012A): This electronic component has been designed and developed for usage in general electronic equipment only. This product is not authorized for use in equipment where a hi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

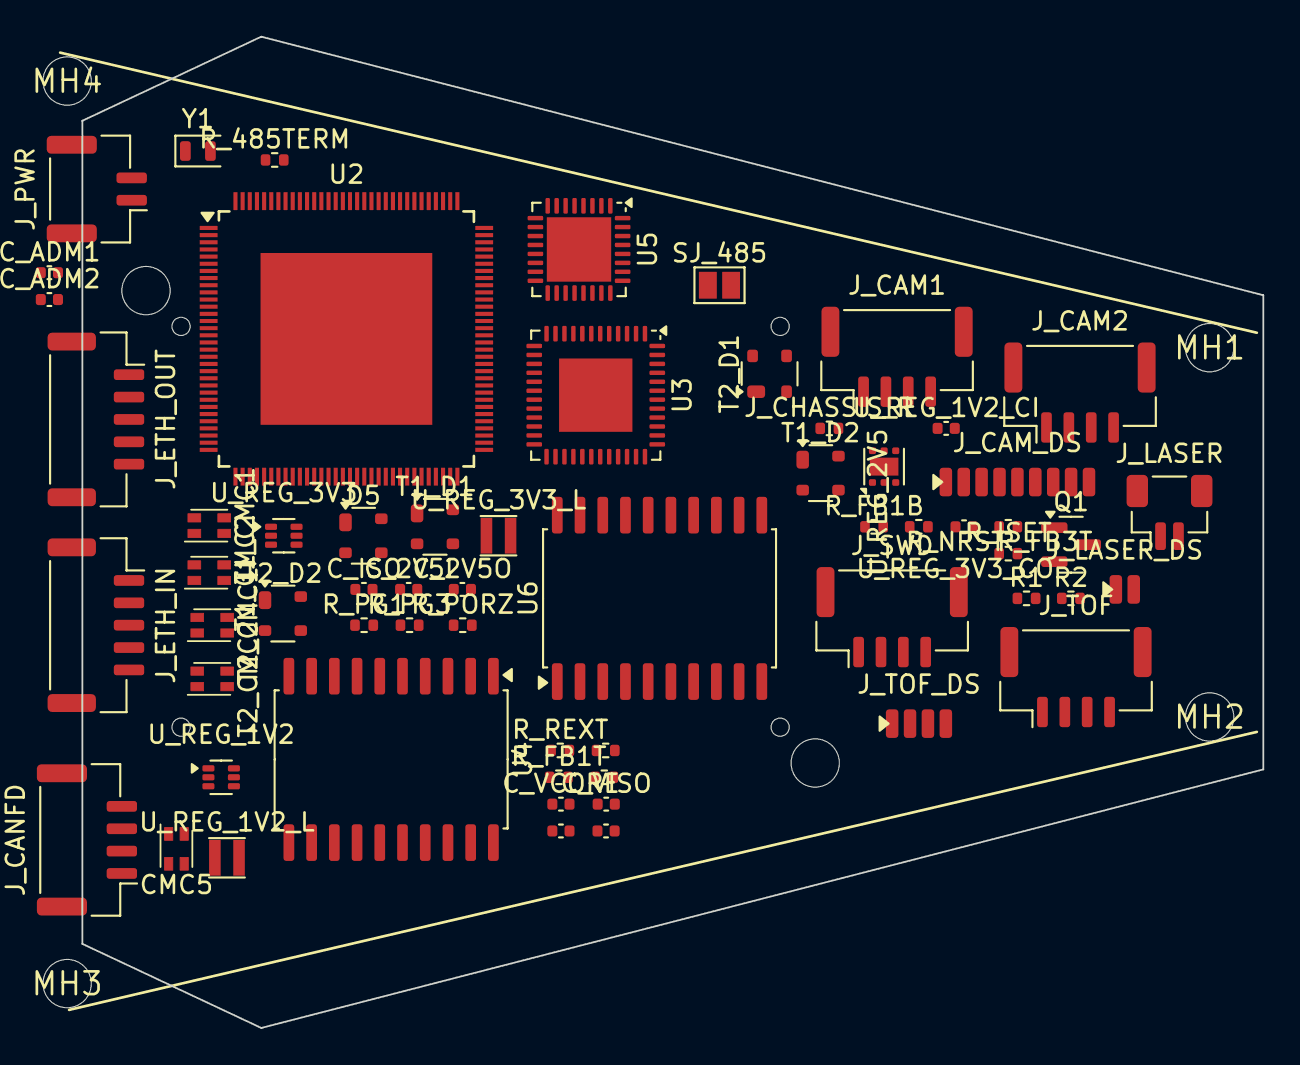
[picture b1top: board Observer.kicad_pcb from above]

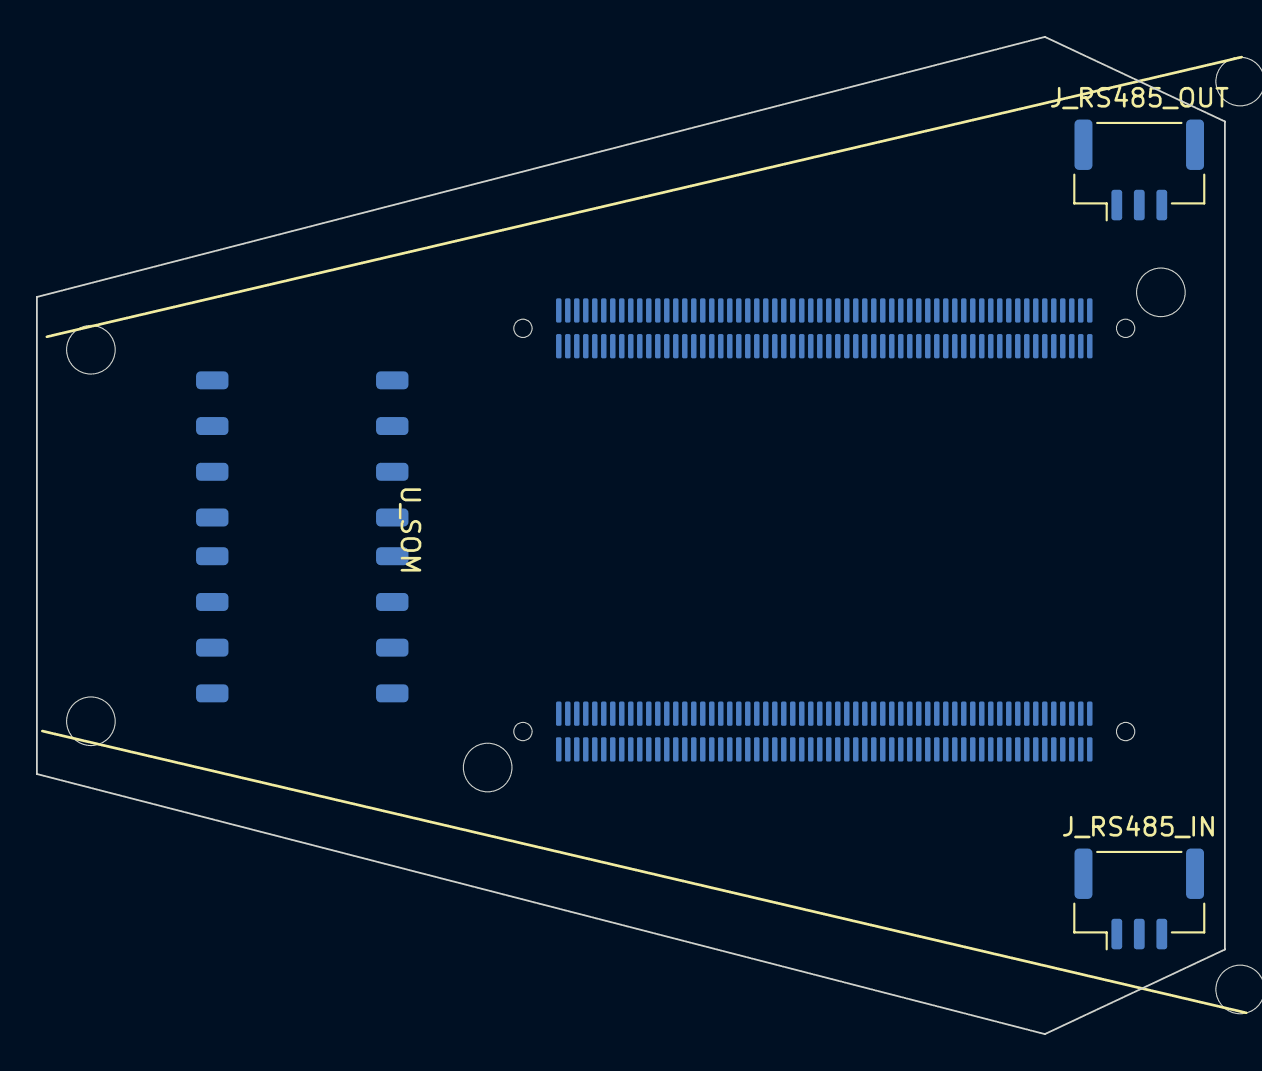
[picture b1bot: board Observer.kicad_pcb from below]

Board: 4 copper layers, 66.0 x 55.4 mm, 70 parts (5 on the bottom side), 100 nets, no tracks yet.

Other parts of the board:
MH1, MH2, MH3, MH4: (no value)

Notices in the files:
avionics/firmware/dts/cape-a/k3-am6254-pocketbeagle2-serenity-cape-a.dts:
SPDX-License-Identifier: CC-BY-4.0
License: CC BY 4.0 — creativecommons.org/licenses/by/4.0
avionics/README.md:
License:
Hardware (PCB schematics, layouts, Gerbers) and the scripts that generate them:** CERN-OHL-W 2.0
Firmware, device trees, and analysis/verification tools:** MIT
All documentation and images:** CC BY-SA 4.0
See root [`LICENSE`](../LICENSE) and [`docs/attribution_and_licensing.md`](../docs/attribution_and_licensing.md)
for full licensing details.
"Can't stop the signal." — River Tam
